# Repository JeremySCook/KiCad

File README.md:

# KiCad
Items relating to KiCad EDA

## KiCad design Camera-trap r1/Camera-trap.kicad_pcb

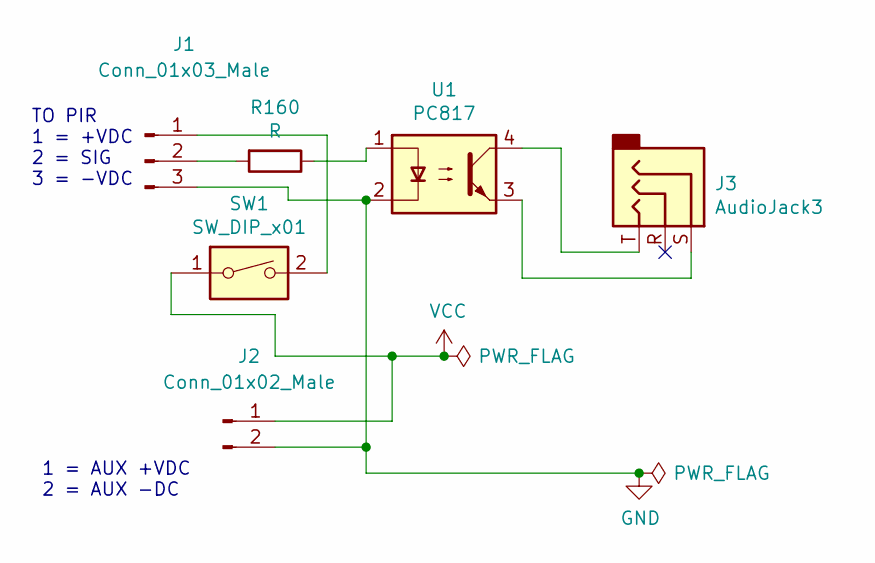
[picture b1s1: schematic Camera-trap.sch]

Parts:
J1: Conn_01x03_Male; PinHeader_1x03_P2.54mm_Vertical
J2: Conn_01x02_Male; PinHeader_1x02_P2.54mm_Vertical
J3: AudioJack3; 2.5mm_jack
R160: R; R_Axial_DIN0207_L6.3mm_D2.5mm_P2.54mm_Vertical
SW1: SW_DIP_x01; SW_DIP_SPSTx01_Slide_9.78x4.72mm_W7.62mm_P2.54mm
U1: PC817; DIP-4_W7.62mm

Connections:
GND: J1.3, J2.2, U1.2
unnamed: J1.1, SW1.2
unnamed: J1.2, R160.2
unnamed: J3.S, U1.3
unnamed: J3.T, U1.4
unnamed: R160.1, U1.1
VCC: J2.1, SW1.1

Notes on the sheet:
TO PIR 1 = +VDC 2 = SIG 3 = -VDC
1 = AUX +VDC 2 = AUX -DC

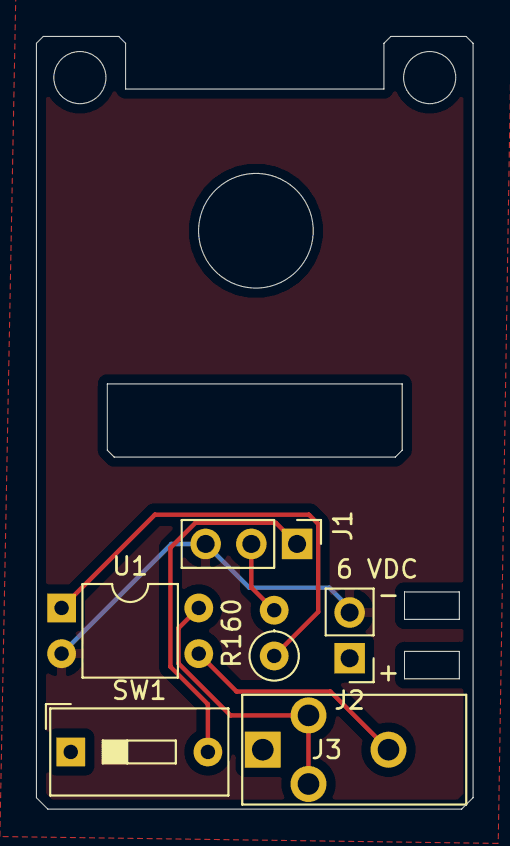
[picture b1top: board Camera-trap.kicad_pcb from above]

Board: 2 copper layers, 24.3 x 42.9 mm, 6 parts (0 on the bottom side), 7 nets.

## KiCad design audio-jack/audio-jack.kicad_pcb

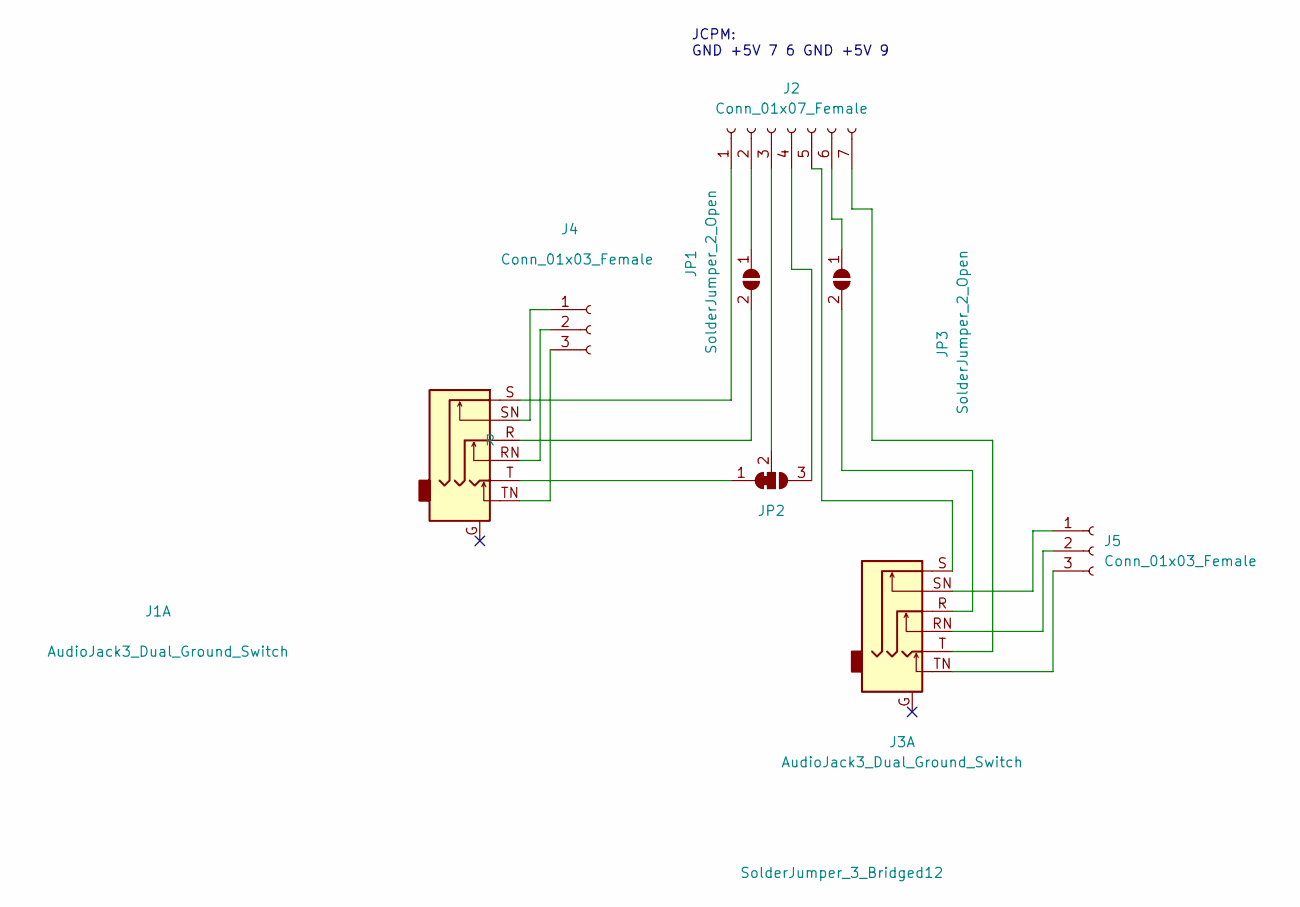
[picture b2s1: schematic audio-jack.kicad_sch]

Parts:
J1, J3: AudioJack3_Dual_Ground_Switch; Jack_6.35mm_Neutrik_NMJ6HCD3_Horizontal
J2: Conn_01x07_Female; PinHeader_1x07_P2.54mm_Horizontal
J4, J5: Conn_01x03_Female; PinHeader_1x03_P2.54mm_Vertical
JP1, JP3: SolderJumper_2_Open; SolderJumper-2_P1.3mm_Open_RoundedPad1.0x1.5mm
JP2: SolderJumper_3_Bridged12; SolderJumper-3_P1.3mm_Bridged12_RoundedPad1.0x1.5mm

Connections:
unnamed: J1.RN, J4.2
unnamed: J1.S, J2.1
unnamed: J1.SN, J4.1
unnamed: J1.TN, J4.3
unnamed: J2.2, JP1.1 (A)
unnamed: J2.3, JP2.2 (C)
unnamed: J2.4, JP2.3 (B)
unnamed: J2.5, J3.S
unnamed: J2.6, JP3.1 (A)
unnamed: J2.7, J3.T
unnamed: J3.R, JP3.2 (B)
unnamed: J3.RN, J5.2
unnamed: J3.SN, J5.1
unnamed: J3.TN, J5.3
unnamed: J1.R, JP1.2 (B)
unnamed: J1.T, JP2.1 (A)

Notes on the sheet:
JCPM: GND +5V 7 6 GND +5V 9

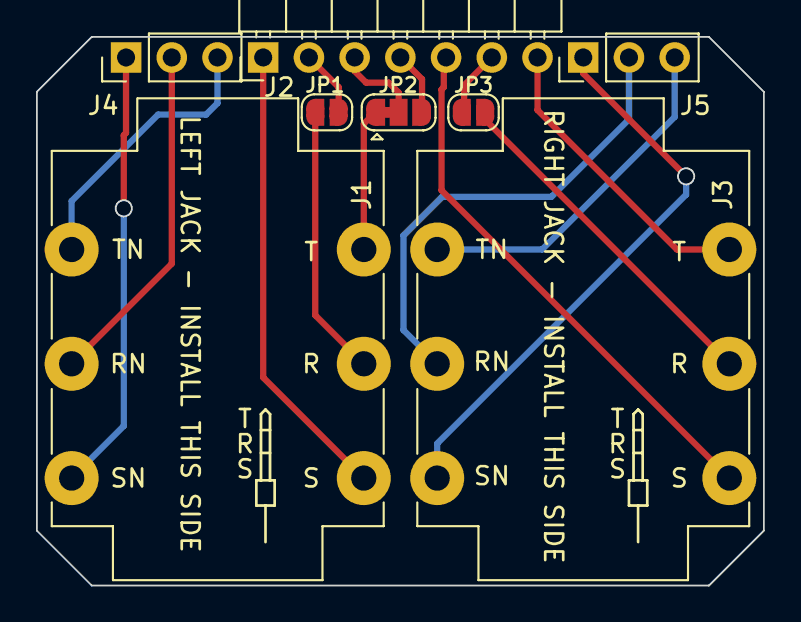
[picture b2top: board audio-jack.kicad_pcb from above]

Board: 2 copper layers, 40.4 x 30.5 mm, 8 parts (0 on the bottom side), 16 nets.

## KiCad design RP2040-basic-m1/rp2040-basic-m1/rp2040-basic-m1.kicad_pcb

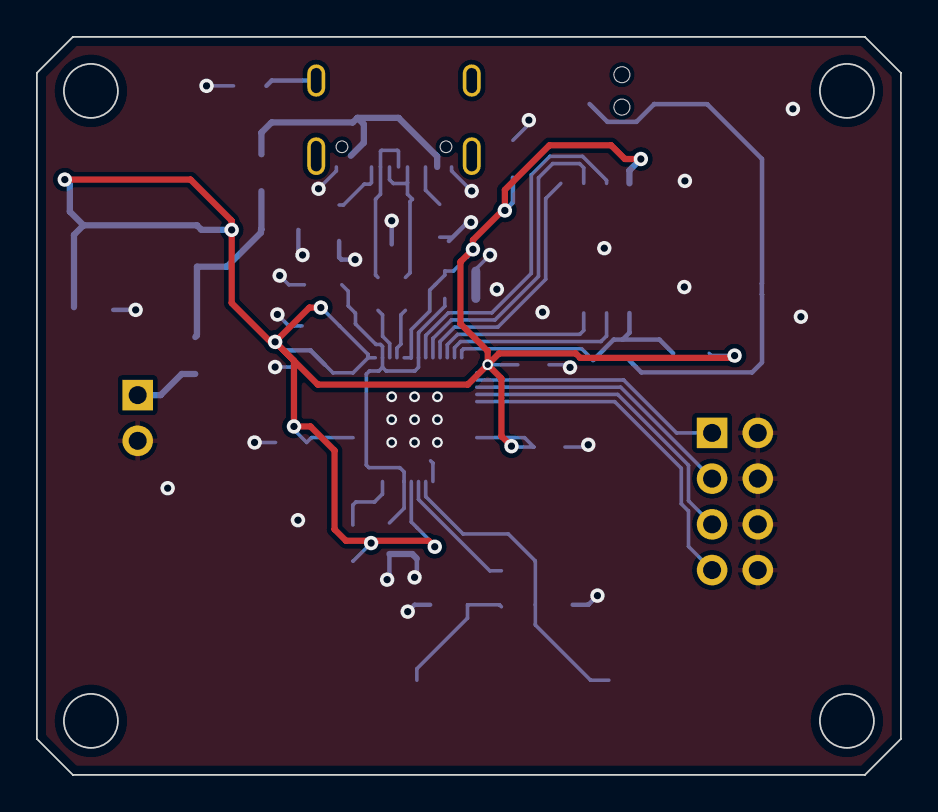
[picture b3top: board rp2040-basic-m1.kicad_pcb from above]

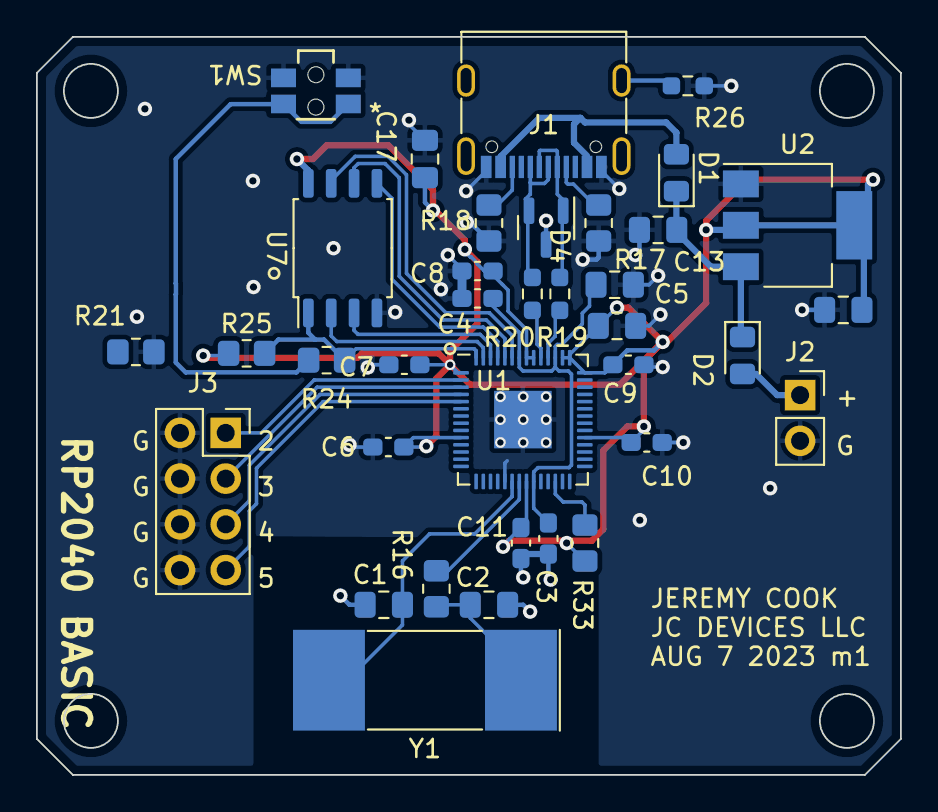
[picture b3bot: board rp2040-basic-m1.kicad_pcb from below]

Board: 2 copper layers, 48.0 x 41.0 mm, 36 parts (36 on the bottom side), 28 nets.

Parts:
C1, C2: 27p; C_0805_2012Metric_Pad1.18x1.45mm_HandSolder
C3, C4, C6, C7, C8, C9, C10, C11: 100n; C_0603_1608Metric_Pad1.08x0.95mm_HandSolder
C5, C12: 1u; C_0805_2012Metric_Pad1.18x1.45mm_HandSolder
C13, C14: 10u; C_0805_2012Metric_Pad1.18x1.45mm_HandSolder
C17: 100n; C_0805_2012Metric_Pad1.18x1.45mm_HandSolder
D1, D2: D_Schottky; D_0805_2012Metric_Pad1.15x1.40mm_HandSolder
D4: D_TVS_Dual_AAC; SOT-23
J1: USB_C_Receptacle_USB2.0; USB_C_Receptacle_G-Switch_GT-USB-7010ASV
J2: Conn_01x02_Pin; PinSocket_1x02_P2.54mm_Vertical
J3: Conn_02x04_Odd_Even; PinSocket_2x04_P2.54mm_Vertical
R16, R24: 1k; R_0805_2012Metric_Pad1.20x1.40mm_HandSolder
R17, R18, R33: 5.1K; R_0805_2012Metric_Pad1.20x1.40mm_HandSolder
R19, R20: 27R; R_0603_1608Metric_Pad0.98x0.95mm_HandSolder
R21: 1M; R_0805_2012Metric_Pad1.20x1.40mm_HandSolder
R25: 10k; R_0805_2012Metric_Pad1.20x1.40mm_HandSolder
R26: 0R; R_0603_1608Metric_Pad0.98x0.95mm_HandSolder
SW1: EVQP7C01P; EVQP7C&slash_L_PAN
U1: RP2040; QFN-56-1EP_7x7mm_P0.4mm_EP3.2x3.2mm
U2: AZ1117CH-3.3TRG1 SOT223-3; SOT-223-3_TabPin2
U7: W25Q128JVS; SOIC-8_5.23x5.23mm_P1.27mm
Y1: Crystal; Crystal_SMD_SeikoEpson_MA505-2Pin_12.7x5.1mm_HandSoldering

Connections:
+1V1: C3.1, C4.1, C5.1, U1.23 (DVDD), U1.45 (VREG_VOUT), U1.50 (DVDD)
+3.3V: C6.1, C7.1, C8.1, C9.1, C10.1, C11.1, C12.1, C14.1, C17.1, R25.1, R33.1, U1.1 (IOVDD), U1.10 (IOVDD), U1.22 (IOVDD), U1.33 (IOVDD), U1.42 (IOVDD), U1.43 (ADC_AVDD), U1.44 (VREG_IN), U1.48 (USB_VDD), U1.49 (IOVDD), U2.2 (VO), U7.8 (VCC)
/usb-power/USB1_DN: D4.1 (A1), J1.A7 (D-), J1.B7 (D-), R19.1
/usb-power/USB1_DP: D4.2 (A2), J1.A6 (D+), J1.B6 (D+), R20.1
GND: C1.1, C2.1, C3.2, C4.2, C5.2, C6.2, C7.2, C8.2, C9.2, C10.2, C11.2, C12.2, C13.2, C14.2, C17.2, D4.3 (common), J1.A1 (GND), J1.A12 (GND), J1.B1 (GND), J1.B12 (GND), J2.2, J3.2, J3.4, J3.6, J3.8, R17.2, R18.2, R21.1, R26.1, SW1.2, SW1.3, U1.19 (TESTEN), U1.57 (GND), U2.1 (GND), U7.4 (GND)
unnamed: C2.2, R16.1, Y1.1
unnamed: D1.2 (A), J1.A4 (VBUS), J1.A9 (VBUS), J1.B4 (VBUS), J1.B9 (VBUS)
unnamed: D2.2 (A), J2.1
unnamed: J1.A5 (CC1), R17.1
unnamed: J1.B5 (CC2), R18.1
unnamed: J1.S1 (SHIELD), R26.2
unnamed: J3.1, U1.2 (GPIO0)
unnamed: J3.3, U1.3 (GPIO1)
unnamed: J3.5, U1.4 (GPIO2)
unnamed: J3.7, U1.5 (GPIO3)
unnamed: R24.1, SW1.1, SW1.4
unnamed: R33.2, U1.26 (RUN)
unnamed: C1.2, U1.20 (XIN), Y1.2
unnamed: R16.2, U1.21 (XOUT)
QSPI_SCLK: U1.52 (QSPI_SCLK), U7.6 (CLK)
QSPI_SD0: U1.53 (QSPI_SD0), U7.5 (DI(IO0))
QSPI_SD2: U1.54 (QSPI_SD2), U7.3 (IO2)
QSPI_SD3: U1.51 (QSPI_SD3), U7.7 (IO3)
QSPI_SS: R24.2, R25.2, U1.56 (QSPI_SS), U7.1 (~CS)
QSPI_SSD1: U1.55 (QSPI_SD1), U7.2 (DO(IO1))
USB_DN: R19.2, U1.46 (USB_DM)
USB_DP: R20.2, U1.47 (USB_DP)
VBUS: C13.1, D1.1 (K), D2.1 (K), U2.3 (VI)
